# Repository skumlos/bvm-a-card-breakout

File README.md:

BVM-A card breakout board

This small PCB can sit between the Sony BVM-A monitors and the expansion cards, to be able to listen in on the communication.

The left connector is a JAE TX25-100P-LT-H1E while the right is a JAE TX24-100R-LT-H1E.

(2020) Martin Hejnfelt, martin@hejnfelt.com

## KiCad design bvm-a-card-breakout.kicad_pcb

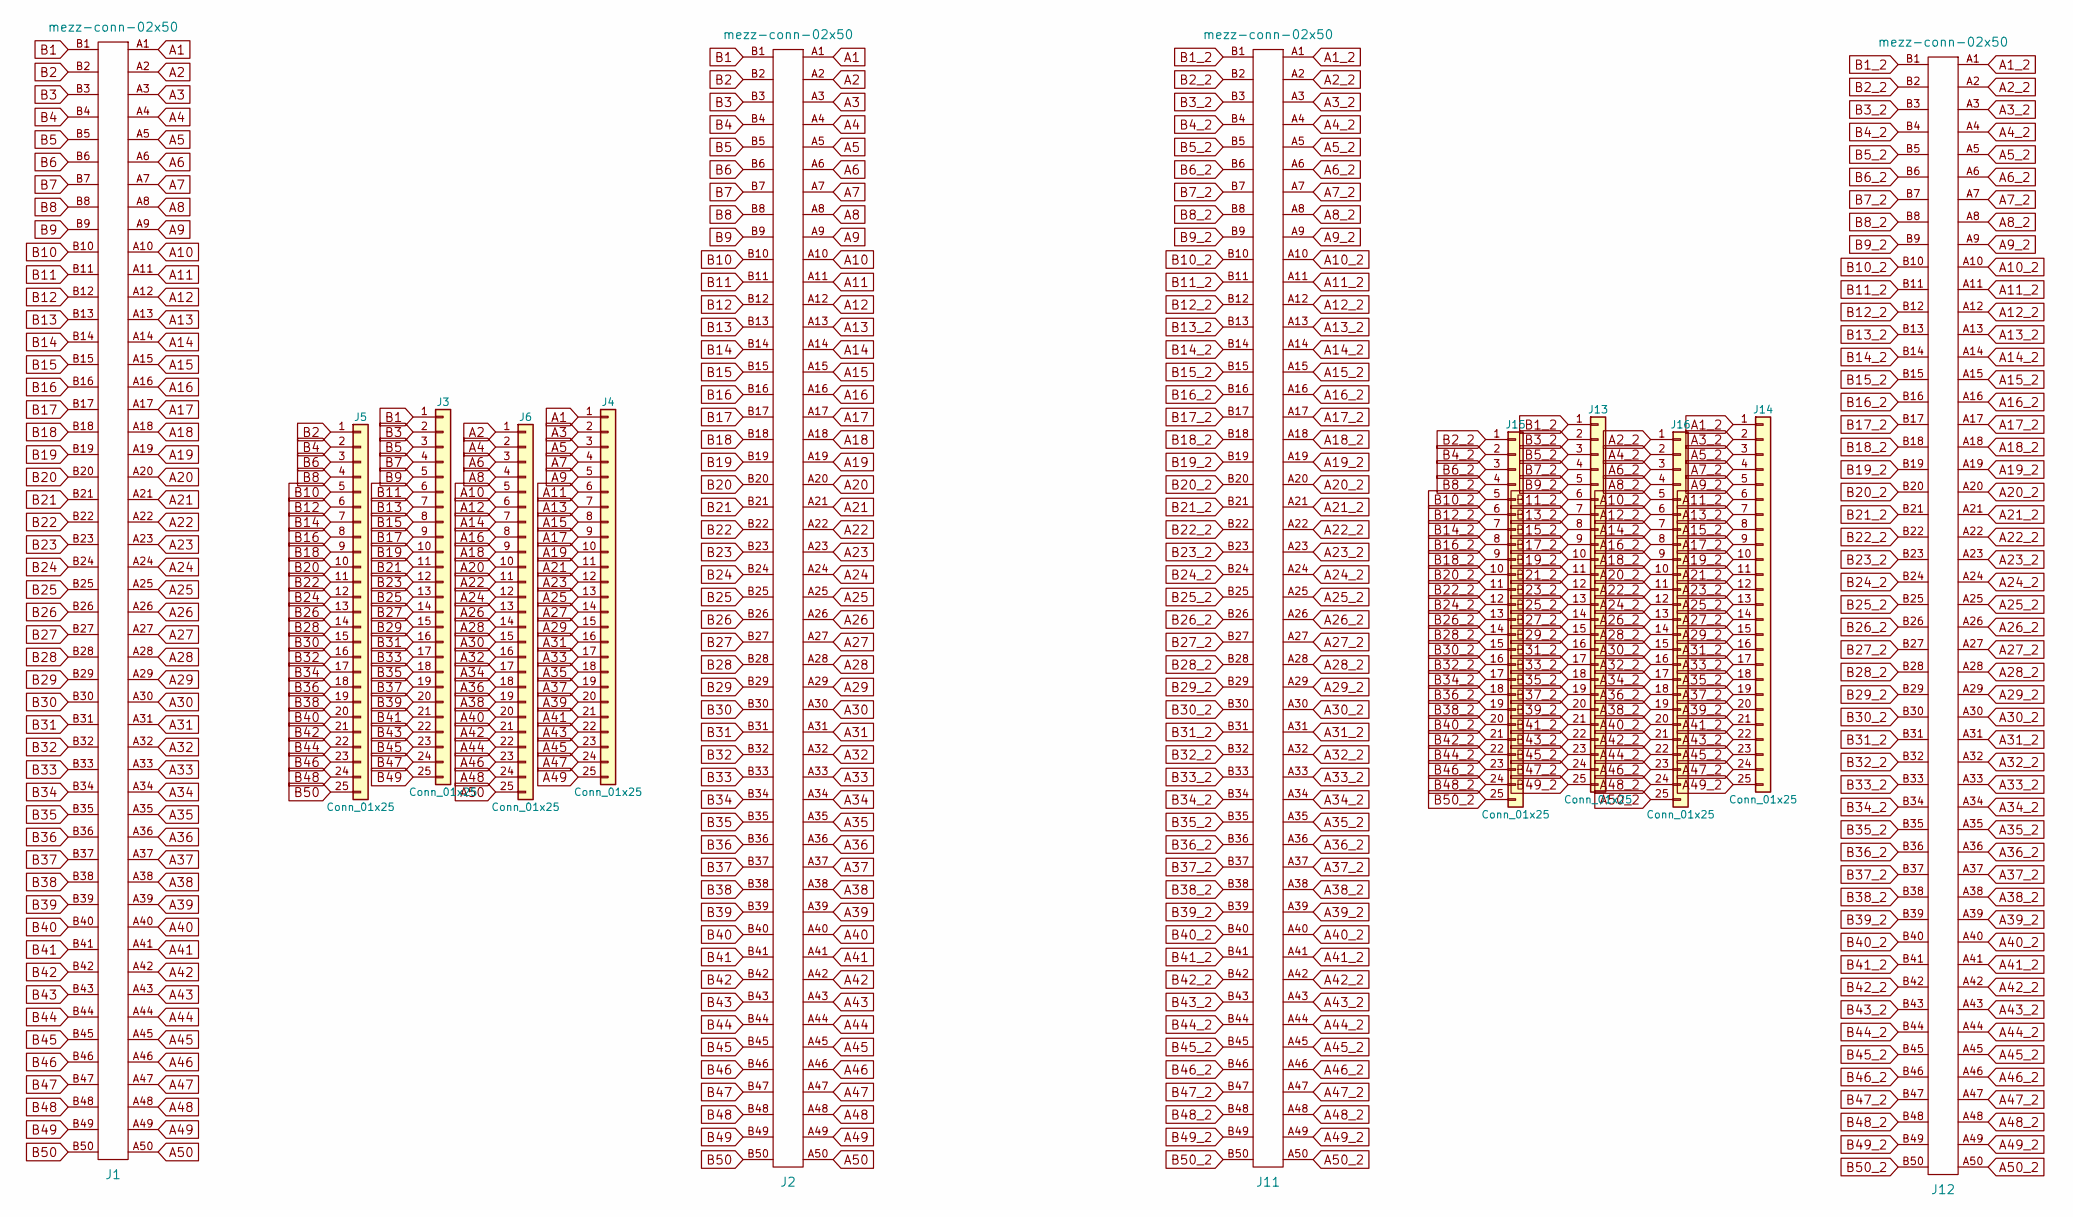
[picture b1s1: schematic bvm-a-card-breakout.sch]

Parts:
J1, J11: mezz-conn-02x50; TX25-100P-LT-H1E
J2, J12: mezz-conn-02x50; TX24-100R-LT-H1E
J3, J4, J5, J6, J13, J14, J15, J16: Conn_01x25; PinHeader_1x25_P2.54mm_Vertical

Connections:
A1: J1.A1, J2.A1, J4.1
A1_2: J11.A1, J12.A1, J14.1
A2: J1.A2, J2.A2, J6.1
A2_2: J11.A2, J12.A2, J16.1
A3: J1.A3, J2.A3, J4.2
A3_2: J11.A3, J12.A3, J14.2
A4: J1.A4, J2.A4, J6.2
A4_2: J11.A4, J12.A4, J16.2
A5: J1.A5, J2.A5, J4.3
A5_2: J11.A5, J12.A5, J14.3
A6: J1.A6, J2.A6, J6.3
A6_2: J11.A6, J12.A6, J16.3
A7: J1.A7, J2.A7, J4.4
A7_2: J11.A7, J12.A7, J14.4
A8: J1.A8, J2.A8, J6.4
A8_2: J11.A8, J12.A8, J16.4
A9: J1.A9, J2.A9, J4.5
A9_2: J11.A9, J12.A9, J14.5
A10: J1.A10, J2.A10, J6.5
A10_2: J11.A10, J12.A10, J16.5
A11: J1.A11, J2.A11, J4.6
A11_2: J11.A11, J12.A11, J14.6
A12: J1.A12, J2.A12, J6.6
A12_2: J11.A12, J12.A12, J16.6
A13: J1.A13, J2.A13, J4.7
A13_2: J11.A13, J12.A13, J14.7
A14: J1.A14, J2.A14, J6.7
A14_2: J11.A14, J12.A14, J16.7
A15: J1.A15, J2.A15, J4.8
A15_2: J11.A15, J12.A15, J14.8
A16: J1.A16, J2.A16, J6.8
A16_2: J11.A16, J12.A16, J16.8
A17: J1.A17, J2.A17, J4.9
A17_2: J11.A17, J12.A17, J14.9
A18: J1.A18, J2.A18, J6.9
A18_2: J11.A18, J12.A18, J16.9
A19: J1.A19, J2.A19, J4.10
A19_2: J11.A19, J12.A19, J14.10
A20: J1.A20, J2.A20, J6.10
A20_2: J11.A20, J12.A20, J16.10
A21: J1.A21, J2.A21, J4.11
A21_2: J11.A21, J12.A21, J14.11
A22: J1.A22, J2.A22, J6.11
A22_2: J11.A22, J12.A22, J16.11
A23: J1.A23, J2.A23, J4.12
A23_2: J11.A23, J12.A23, J14.12
A24: J1.A24, J2.A24, J6.12
A24_2: J11.A24, J12.A24, J16.12
A25: J1.A25, J2.A25, J4.13
A25_2: J11.A25, J12.A25, J14.13
A26: J1.A26, J2.A26, J6.13
A26_2: J11.A26, J12.A26, J16.13
A27: J1.A27, J2.A27, J4.14
A27_2: J11.A27, J12.A27, J14.14
A28: J1.A28, J2.A28, J6.14
A28_2: J11.A28, J12.A28, J16.14
A29: J1.A29, J2.A29, J4.15
A29_2: J11.A29, J12.A29, J14.15
A30: J1.A30, J2.A30, J6.15
A30_2: J11.A30, J12.A30, J16.15
A31: J1.A31, J2.A31, J4.16
A31_2: J11.A31, J12.A31, J14.16
A32: J1.A32, J2.A32, J6.16
A32_2: J11.A32, J12.A32, J16.16
A33: J1.A33, J2.A33, J4.17
A33_2: J11.A33, J12.A33, J14.17
A34: J1.A34, J2.A34, J6.17
A34_2: J11.A34, J12.A34, J16.17
A35: J1.A35, J2.A35, J4.18
A35_2: J11.A35, J12.A35, J14.18
A36: J1.A36, J2.A36, J6.18
A36_2: J11.A36, J12.A36, J16.18
A37: J1.A37, J2.A37, J4.19
A37_2: J11.A37, J12.A37, J14.19
A38: J1.A38, J2.A38, J6.19
A38_2: J11.A38, J12.A38, J16.19
A39: J1.A39, J2.A39, J4.20
A39_2: J11.A39, J12.A39, J14.20
A40: J1.A40, J2.A40, J6.20
A40_2: J11.A40, J12.A40, J16.20
A41: J1.A41, J2.A41, J4.21
A41_2: J11.A41, J12.A41, J14.21
A42: J1.A42, J2.A42, J6.21
A42_2: J11.A42, J12.A42, J16.21
A43: J1.A43, J2.A43, J4.22
A43_2: J11.A43, J12.A43, J14.22
A44: J1.A44, J2.A44, J6.22
A44_2: J11.A44, J12.A44, J16.22
A45: J1.A45, J2.A45, J4.23
A45_2: J11.A45, J12.A45, J14.23
A46: J1.A46, J2.A46, J6.23
A46_2: J11.A46, J12.A46, J16.23
A47: J1.A47, J2.A47, J4.24
A47_2: J11.A47, J12.A47, J14.24
A48: J1.A48, J2.A48, J6.24
A48_2: J11.A48, J12.A48, J16.24
A49: J1.A49, J2.A49, J4.25
A49_2: J11.A49, J12.A49, J14.25
A50: J1.A50, J2.A50, J6.25
A50_2: J11.A50, J12.A50, J16.25
B1: J1.B1, J2.B1, J3.1
B1_2: J11.B1, J12.B1, J13.1
B2: J1.B2, J2.B2, J5.1
B2_2: J11.B2, J12.B2, J15.1
B3: J1.B3, J2.B3, J3.2
B3_2: J11.B3, J12.B3, J13.2
B4: J1.B4, J2.B4, J5.2
B4_2: J11.B4, J12.B4, J15.2
B5: J1.B5, J2.B5, J3.3
B5_2: J11.B5, J12.B5, J13.3
B6: J1.B6, J2.B6, J5.3
B6_2: J11.B6, J12.B6, J15.3
B7: J1.B7, J2.B7, J3.4
B7_2: J11.B7, J12.B7, J13.4
B8: J1.B8, J2.B8, J5.4
B8_2: J11.B8, J12.B8, J15.4
B9: J1.B9, J2.B9, J3.5
B9_2: J11.B9, J12.B9, J13.5
B10: J1.B10, J2.B10, J5.5
B10_2: J11.B10, J12.B10, J15.5
B11: J1.B11, J2.B11, J3.6
B11_2: J11.B11, J12.B11, J13.6
B12: J1.B12, J2.B12, J5.6
B12_2: J11.B12, J12.B12, J15.6
B13: J1.B13, J2.B13, J3.7
B13_2: J11.B13, J12.B13, J13.7
B14: J1.B14, J2.B14, J5.7
B14_2: J11.B14, J12.B14, J15.7
B15: J1.B15, J2.B15, J3.8
B15_2: J11.B15, J12.B15, J13.8
B16: J1.B16, J2.B16, J5.8
B16_2: J11.B16, J12.B16, J15.8
B17: J1.B17, J2.B17, J3.9
B17_2: J11.B17, J12.B17, J13.9
B18: J1.B18, J2.B18, J5.9
B18_2: J11.B18, J12.B18, J15.9
B19: J1.B19, J2.B19, J3.10
B19_2: J11.B19, J12.B19, J13.10
B20: J1.B20, J2.B20, J5.10
B20_2: J11.B20, J12.B20, J15.10
B21: J1.B21, J2.B21, J3.11
B21_2: J11.B21, J12.B21, J13.11
B22: J1.B22, J2.B22, J5.11
B22_2: J11.B22, J12.B22, J15.11
B23: J1.B23, J2.B23, J3.12
B23_2: J11.B23, J12.B23, J13.12
B24: J1.B24, J2.B24, J5.12
B24_2: J11.B24, J12.B24, J15.12
B25: J1.B25, J2.B25, J3.13
B25_2: J11.B25, J12.B25, J13.13
B26: J1.B26, J2.B26, J5.13
B26_2: J11.B26, J12.B26, J15.13
B27: J1.B27, J2.B27, J3.14
B27_2: J11.B27, J12.B27, J13.14
B28: J1.B28, J2.B28, J5.14
B28_2: J11.B28, J12.B28, J15.14
B29: J1.B29, J2.B29, J3.15
B29_2: J11.B29, J12.B29, J13.15
B30: J1.B30, J2.B30, J5.15
B30_2: J11.B30, J12.B30, J15.15
B31: J1.B31, J2.B31, J3.16
B31_2: J11.B31, J12.B31, J13.16
B32: J1.B32, J2.B32, J5.16
B32_2: J11.B32, J12.B32, J15.16
B33: J1.B33, J2.B33, J3.17
B33_2: J11.B33, J12.B33, J13.17
B34: J1.B34, J2.B34, J5.17
B34_2: J11.B34, J12.B34, J15.17
B35: J1.B35, J2.B35, J3.18
B35_2: J11.B35, J12.B35, J13.18
B36: J1.B36, J2.B36, J5.18
B36_2: J11.B36, J12.B36, J15.18
B37: J1.B37, J2.B37, J3.19
B37_2: J11.B37, J12.B37, J13.19
B38: J1.B38, J2.B38, J5.19
B38_2: J11.B38, J12.B38, J15.19
B39: J1.B39, J2.B39, J3.20
B39_2: J11.B39, J12.B39, J13.20
B40: J1.B40, J2.B40, J5.20
B40_2: J11.B40, J12.B40, J15.20
B41: J1.B41, J2.B41, J3.21
B41_2: J11.B41, J12.B41, J13.21
B42: J1.B42, J2.B42, J5.21
B42_2: J11.B42, J12.B42, J15.21
B43: J1.B43, J2.B43, J3.22
B43_2: J11.B43, J12.B43, J13.22
B44: J1.B44, J2.B44, J5.22
B44_2: J11.B44, J12.B44, J15.22
B45: J1.B45, J2.B45, J3.23
B45_2: J11.B45, J12.B45, J13.23
B46: J1.B46, J2.B46, J5.23
B46_2: J11.B46, J12.B46, J15.23
B47: J1.B47, J2.B47, J3.24
B47_2: J11.B47, J12.B47, J13.24
B48: J1.B48, J2.B48, J5.24
B48_2: J11.B48, J12.B48, J15.24
B49: J1.B49, J2.B49, J3.25
B49_2: J11.B49, J12.B49, J13.25
B50: J1.B50, J2.B50, J5.25
B50_2: J11.B50, J12.B50, J15.25

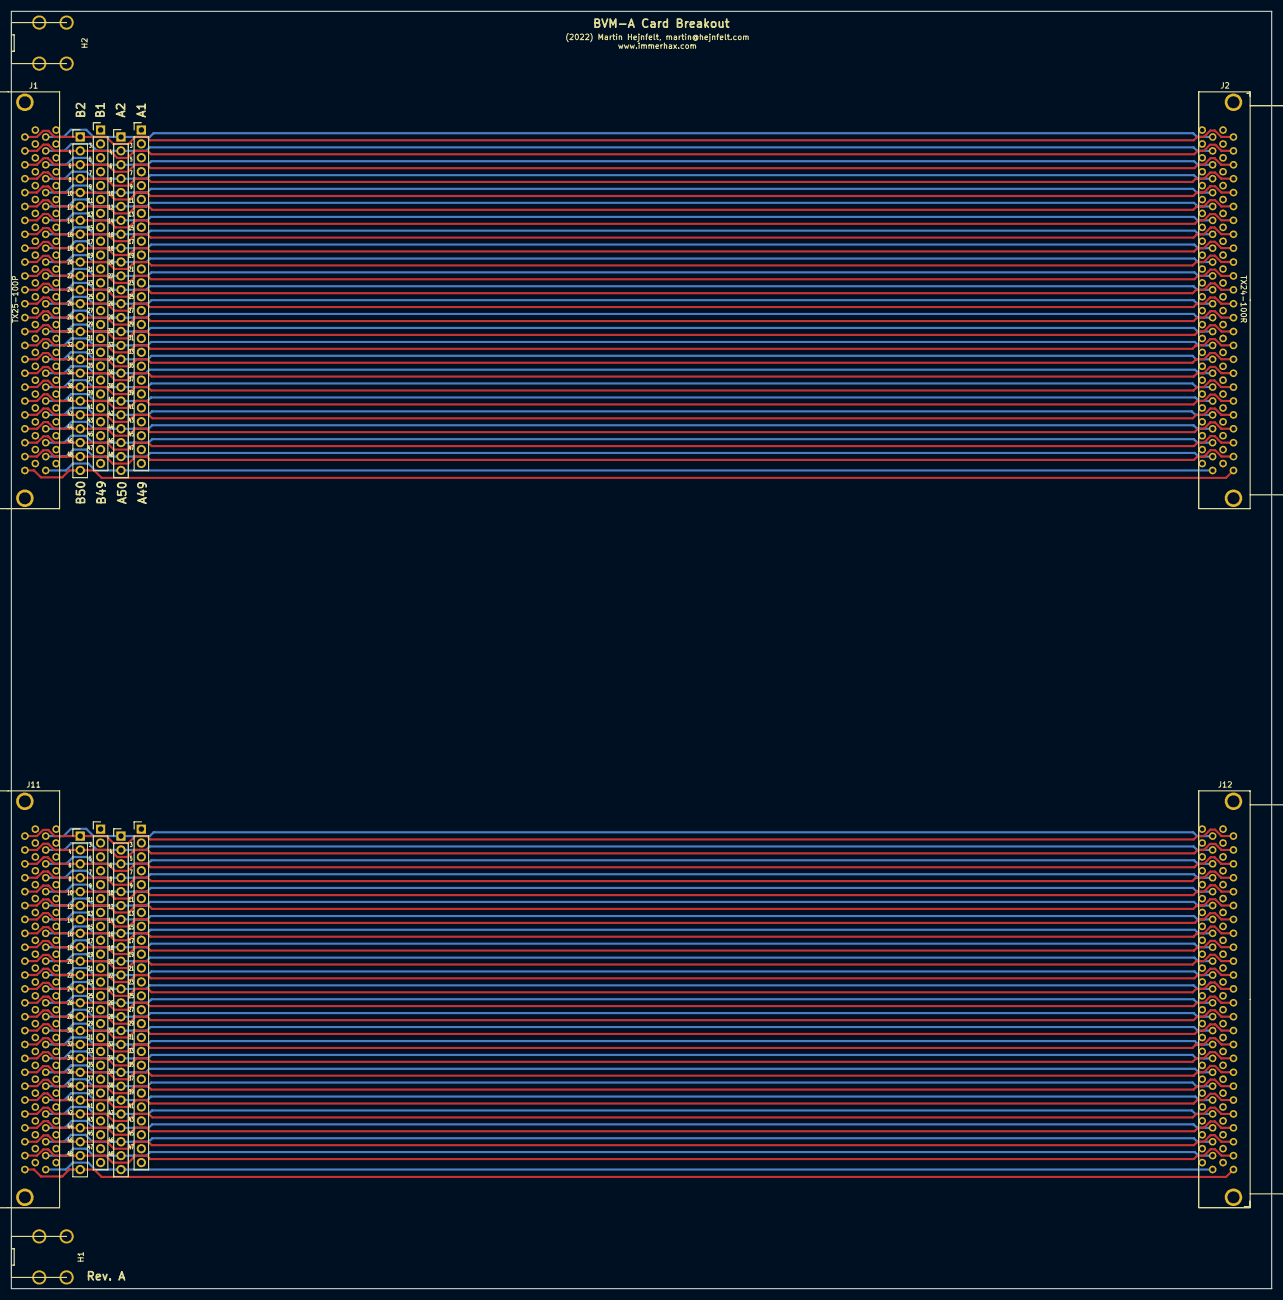
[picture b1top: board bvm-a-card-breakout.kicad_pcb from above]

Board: 4 copper layers, 230.4 x 233.5 mm, 14 parts (0 on the bottom side), 200 nets.

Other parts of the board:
H1, H2: Keystone 7794; 7794-X

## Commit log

2020-10-08 Fixed slight misalignment in connector footprints
2022-06-08 Updated to full-size Z-board replacement
